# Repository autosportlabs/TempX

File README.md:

TempX
=====

TempX is a temperature sensor breakout board for the TMP36 active temperature sensor.

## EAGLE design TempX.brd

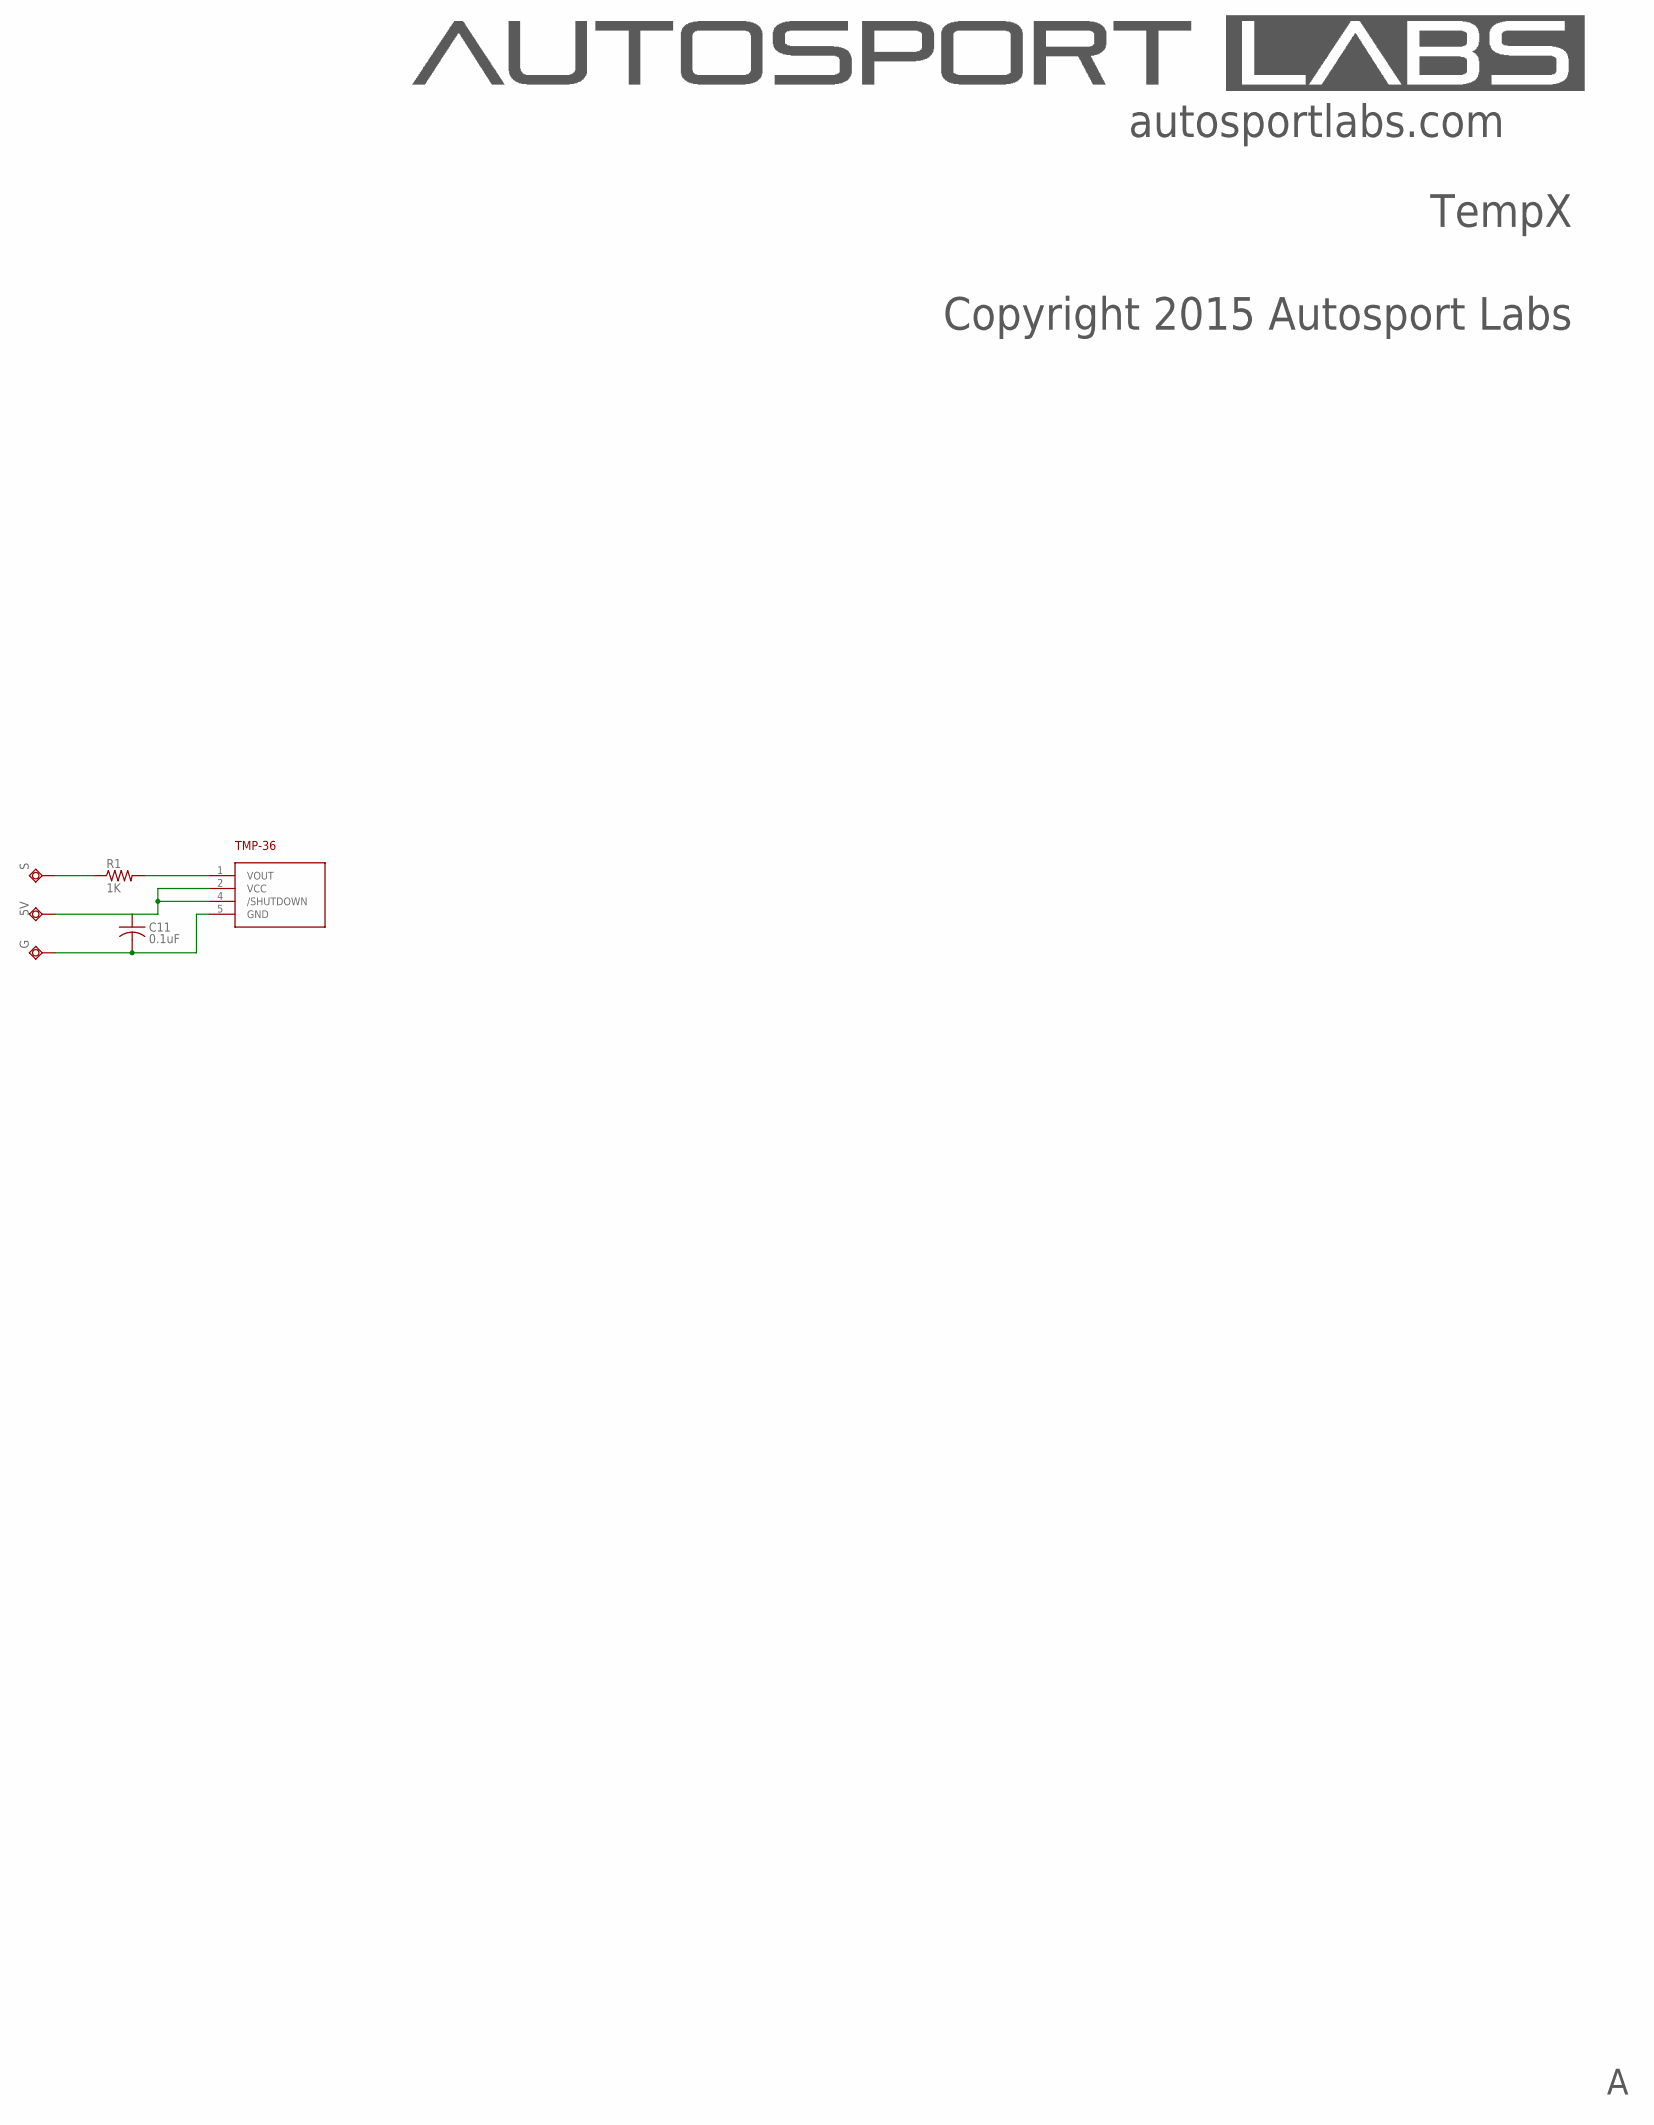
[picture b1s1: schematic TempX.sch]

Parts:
5V: TPSQPAD1-17; P1-17
C11: 0.1uF; C0603
G: TPSQPAD1-17; P1-17
R1: 1K; R0603
S: TPSQPAD1-17; P1-17
U1: TMP36; SOT-23

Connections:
5V: 5V.TP, C11.1, U1.2 (VCC), U1.4 (/SHUTDOWN)
C1: C11.2, G.TP, U1.5 (GND)
unnamed: R1.1, S.TP
unnamed: R1.2, U1.1 (VOUT)

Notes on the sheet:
Copyright 2015 Autosport Labs
TempX
autosportlabs.com

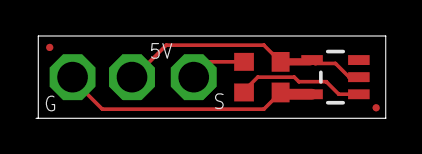
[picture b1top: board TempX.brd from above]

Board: 2 copper layers, 19.3 x 4.6 mm, 6 parts (0 on the bottom side), 4 nets.

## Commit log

2015-01-01 initial checkin
2015-01-01 added screenshot of board
2015-01-05 made board slimmer
2016-10-26 changed design to circular
2016-10-26 fixed some DRC issues
2017-06-09 move silkscreen around
2018-04-04 change layout to rectangle
2018-04-04 update image
